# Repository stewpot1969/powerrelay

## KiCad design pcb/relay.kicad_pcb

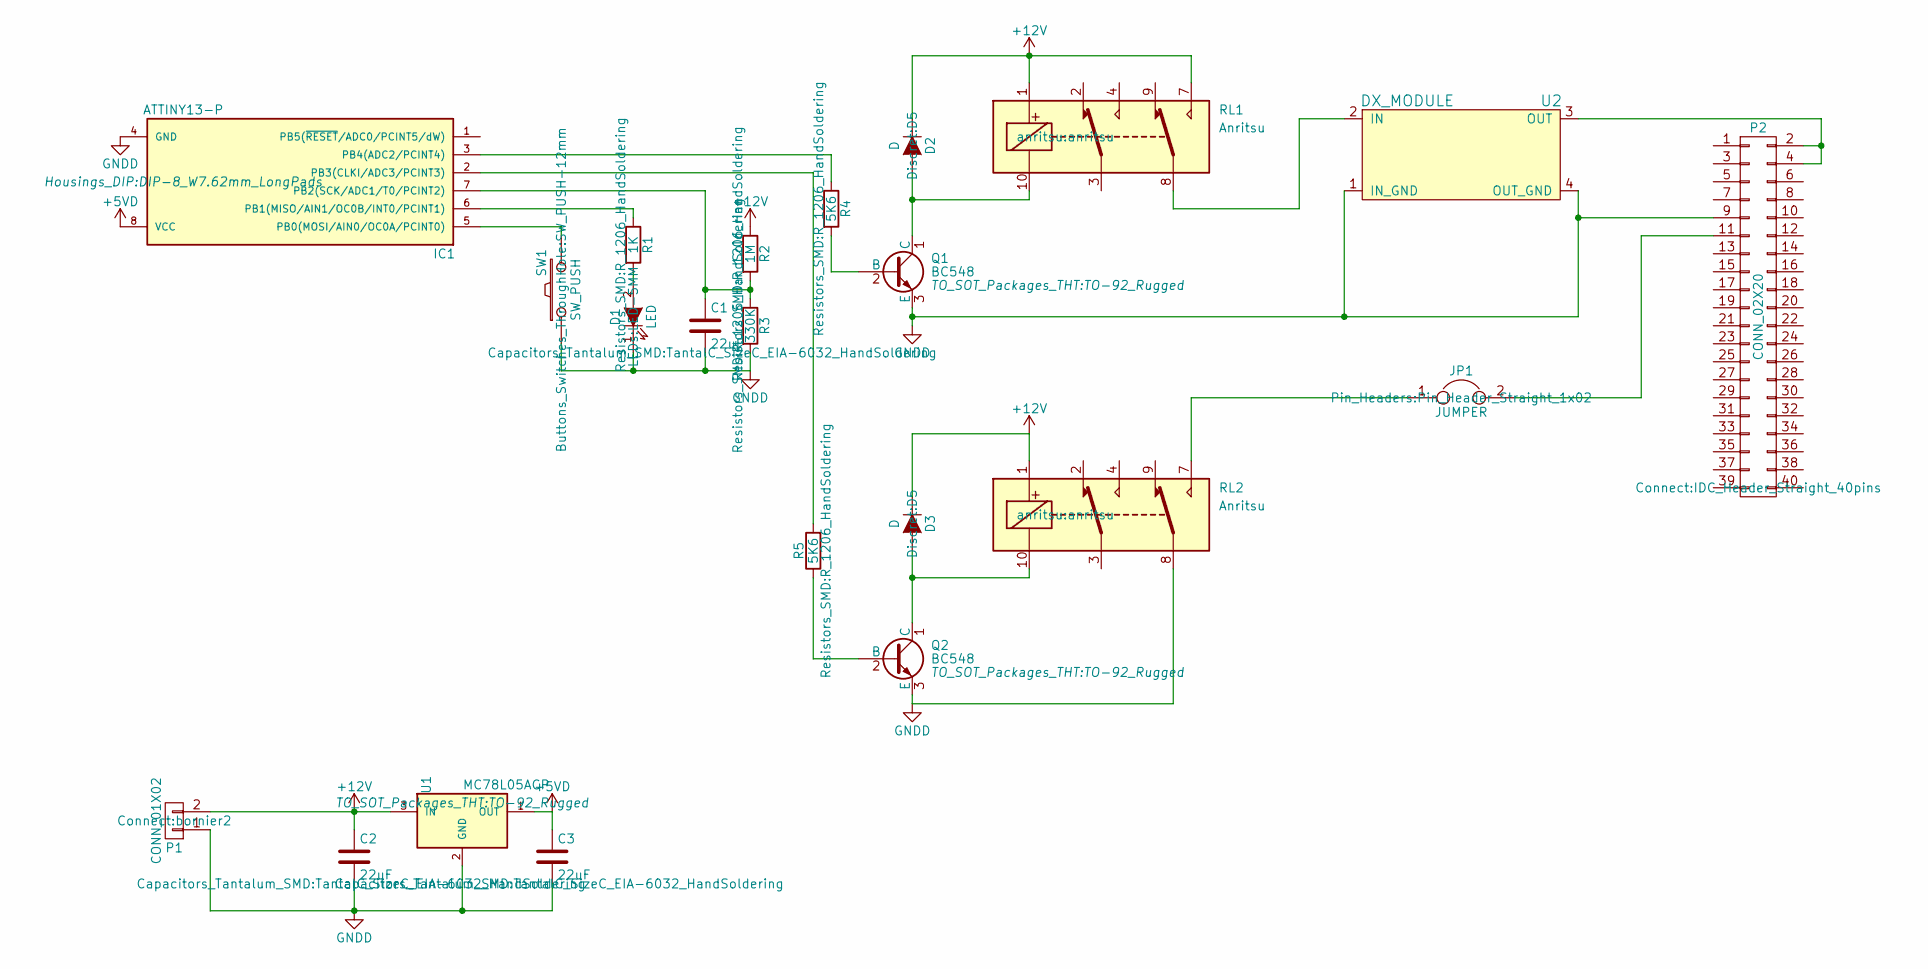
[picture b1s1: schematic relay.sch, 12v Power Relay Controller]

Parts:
C1, C2, C3: 22uF; TantalC_SizeC_EIA-6032_HandSoldering
D1: LED; LED-5MM
D2, D3: D; D5
IC1: ATTINY13-P; DIP-8_W7.62mm_LongPads
JP1: JUMPER; Pin_Header_Straight_1x02
P1: CONN_01X02; bornier2
P2: CONN_02X20; IDC_Header_Straight_40pins
Q1, Q2: BC548; TO-92_Rugged
R1: 1K; R_1206_HandSoldering
R2: 1M; R_1206_HandSoldering
R3: 330K; R_1206_HandSoldering
R4, R5: 5K6; R_1206_HandSoldering
RL1, RL2: Anritsu; anritsu
SW1: SW_PUSH; SW_PUSH-12mm
U1: MC78L05ACP; TO-92_Rugged
U2: DX_MODULE; dx_module

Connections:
+5VD: C3.1, IC1.8 (VCC), U1.1 (OUT)
+12V: C2.1, D2.1 (K), D3.1 (K), P1.2, R2.1, RL1.1, RL1.7, RL2.1, U1.3 (IN)
GNDD: C1.2, C2.2, C3.2, D1.1 (K), IC1.4 (GND), P1.1, P2.9, Q1.3 (E), Q2.3 (E), R3.2, RL2.8, SW1.1, U1.2 (GND), U2.1 (IN_GND), U2.4 (OUT_GND)
unnamed: C1.1, IC1.7 (PB2(SCK/ADC1/T0/PCINT2)), R2.2, R3.1
unnamed: D1.2 (A), R1.2
unnamed: D2.2 (A), Q1.1 (C), RL1.10
unnamed: D3.2 (A), Q2.1 (C), RL2.10
unnamed: IC1.2 (PB3(CLKI/ADC3/PCINT3)), R5.2
unnamed: IC1.3 (PB4(ADC2/PCINT4)), R4.1
unnamed: IC1.5 (PB0(MOSI/AIN0/OC0A/PCINT0)), SW1.2
unnamed: IC1.6 (PB1(MISO/AIN1/OC0B/INT0/PCINT1)), R1.1
unnamed: JP1.1, RL2.7
unnamed: JP1.2, P2.11
unnamed: P2.2, P2.4, U2.3 (OUT)
unnamed: Q1.2 (B), R4.2
unnamed: Q2.2 (B), R5.1
unnamed: RL1.8, U2.2 (IN)

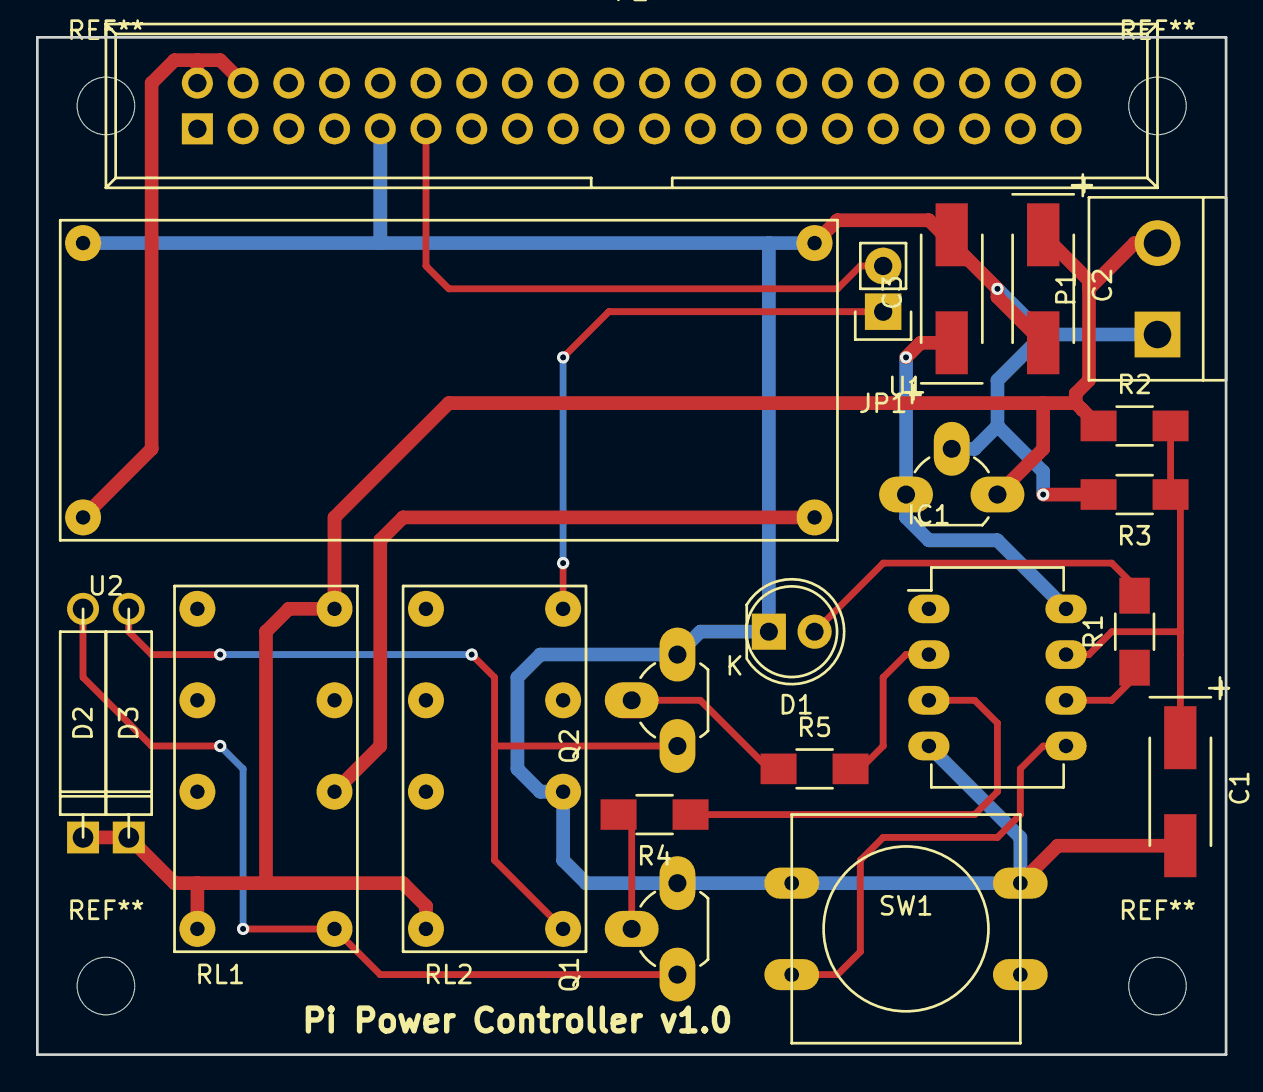
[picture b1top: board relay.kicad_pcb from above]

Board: 2 copper layers, 66.0 x 56.5 mm, 22 parts (0 on the bottom side), 17 nets.

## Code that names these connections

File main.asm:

;  file to control a relay

.nolist
.include "tn13def.inc"
.list

; VOLTAGE LEVELS
; ADC result = 50.8*voltage - 2.39
.define   V_HIGH            668     ; ~13.2V
.define   V_LOW             617     ; ~12.2V

; temp reg for things
.def  scratch = r23
; timer countdown for state changes etc
.def  count   = r24
.define   COUNT_PRE_ON      10   ; seconds of engine-on volts before bootup
.define   COUNT_PRE_OFF     20    ; seconds from shutdown relay on to power off
.define   COUNT_PRE_SHUT    180     ; secs of engine-off volts before shutdown

; prescaler for second counter
.def  count2  = r25
.define   COUNT2_PRESCALE   4

; state of the switch
.def  state   = r26
.define   STATE_IDLE        1   ; resting state
.define   STATE_PRE_ON      2   ; engine started
.define   STATE_ON          4   ; power on to Pi
.define   STATE_PRE_SHUT    8   ; engine turned off, Pi still running
.define   STATE_PRE_OFF     16  ; shutdown relay on, Pi shutting down
.define   STATE_MANUAL      32  ; button has been pressed

; state of the voltage input
.def  v_state = r27
.define   V_STATE_SICK      1     ; <12.2V - battery getting down
.define   V_STATE_OK        2     ; 12.2-13.2V  - engine off, battery OK
.define   V_STATE_HIGH      4     ; >13.2V - engine running
.define   V_STATE_BUTTON    8     ; button pushed


.macro    set_output
    in    r16,DDR@0
    ori   r16,1<<@1
    out   DDR@0,r16
.endm
.macro    set_pullup
    in    r16,PORT@0
    ori   r16,1<<@1
    out   PORT@0,r16
.endm
.macro    set_high
    in    r16,PORT@0
    ori   r16,1<<@1
    out   PORT@0,r16
.endm
.macro    set_low
    in    r16,PORT@0
    andi  r16,255-(1<<@1)
    out   PORT@0,r16
.endm

.dseg
.org  SRAM_START

; myval:    .byte 1

.cseg
.org          0x0000


reset:
    ldi     r16,low(RAMEND)
    out     SPL,r16

    ; setup I/O
    ; 1: _reset
    ; 2: PB3 - relay out
    ; 3: PB4 - 2nd relay?
    ; 4: GND
    ; 5: PB0 - button
    ; 6: PB1 - indicator LED
    ; 7: PB2 - ADC1 - sys V in
    ; 8: 5V
    ldi   r16,(1<<1)|(1<<3)|(1<<4)
    out   DDRB,r16
    ;set_output  B,1       ; PB1 LED out
    ;set_output  B,3       ; PB3 relay 1 out
    ;set_output  B,4       ; PB4 relay 2 out
    set_pullup  B,0       ; PB0 button pullup

    ; setup ADC (Vref=Vcc, /8 prescaler (125kHz))
    ; PB2 (ADC1), ADLAR=0
    
    ldi     r16,1     ; Vref=Vcc, ADLAR=0, MUX1=1 (ADC1 PB2)
    out     ADMUX,r16
    
    ldi     r16,(1<<ADEN)+3 ; enable ADC, /8
    out     ADCSRA,r16
    
    ; setup timer0
    ; compare output modes normal, WGM=CTC
    ldi     r16,0b00000010
    out     TCCR0A,r16
    ; WGM=CTC, clock prescaler = 1024
    ldi     r16,0b00000101
    out     TCCR0B,r16
    ; overflow every 250 cycles = 0.5 seconds
    ldi     r16,250
    out     OCR0A,r16

    ; prepare states and stuff for the loop
    ldi     count,-1        ; timer off
    ldi     state,STATE_IDLE    ; state=IDLE
    ldi     count2,COUNT2_PRESCALE  ; load prescaler

loop:
    
    ; step 1: wait for the interrupt flag to be set
    in    r16,TIFR0
    sbrs  r16,OCF0A
    rjmp  loop
    
    ; step 2: clear interrupt flag
    ldi   r16,1<<OCF0A
    out   TIFR0,r16

    ; step 3 - read ADC
    ldi     r16,(1<<ADEN)+(1<<ADSC)+1   ; start conversion
    out     ADCSRA,r16
wfadc:
    in      r16,ADCSRA
    andi    r16,(1<<ADIF)     ; check if ADIF is set (ADC complete)
    breq    wfadc

    ; step 4 - look at the voltage
    in      r16,ADCL
    in      r17,ADCH
    ldi     r18,low(V_HIGH)
    ldi     r19,high(V_HIGH)
    cp      r16,r18     ; subtract V_HIGH from ADC
    cpc     r17,r19
    brcs    s4_1    ; branch if ADC < V_HIGH
    ldi     v_state,V_STATE_HIGH
    rjmp    s5
s4_1:
    ldi     r18,low(V_LOW)
    ldi     r19,high(V_LOW)
    cp      r16,r18   ; subtract V_LOW from ADC
    cpc     r17,r19
    brcs    s4_2      ; branch if ADC < V_LOW
    ldi     v_state,V_STATE_OK
    rjmp    s5
s4_2:
    ldi     v_state,V_STATE_SICK
    
    ; step 5  - check button, decrement timer prescaler and timer
s5:
    in    r16,PINB
    andi  r16,1     ; check bit 0
    brne  s5_1      ; PINB.0=1 = no button
    ori   v_state,V_STATE_BUTTON
s5_1:
    dec   count2
    brne  loop      ; no prescale zero? All done for this time
    ldi   count2,COUNT2_PRESCALE    ; reload prescaler
    cpi   count,-1      ; count=-1 means counter not being used
    breq  s6
    dec   count


    ; step 6 - split out based on state
s6:
    ldi   ZL,low(calltable*2)
    ldi   ZH,high(calltable*2)
s6_1:
    lpm   r16,Z+    ; r16=V_STATE mask
    tst   r16
    breq  loop      ; table ends in zero
    lpm   r17,Z+    ; r17=STATE mask
    lpm   YL,Z+     ; save subroutine address in Y
    lpm   YH,Z+
    and   r16,v_state   ; and v_state with v_state mask
    breq  s6_1      ; no overlap? go to next entry in calltable
    and   r17,state     ; now check state mask
    breq  s6_1        ; no overlap? next entry
    mov   ZH,YH       ; move Y to Z
    mov   ZL,YL
    icall           ; call subroutine pointed to by Z
    rjmp  loop    

;========================================================
; SUBROUTINES POINTED TO BY CALLTABLE:

idleoff:    ; go into idle mode
  ldi   state,STATE_IDLE
  ldi   count,-1
  in    r16,PORTB
  andi  r16,0b11100101  ; 1,3,4 off = power,shutdown,LED
  out   PORTB,r16
  ret  
  
preshut:    ; sets state=PRE_SHUT
  ldi   state,STATE_PRE_SHUT
  ldi   count,COUNT_PRE_SHUT
  ret
  
preoff:   ;state=PRE_SHUT,Vok
  tst   count     ; timer before setting shutdown relay
  brne  preoff_2
  ldi   state,STATE_PRE_OFF
  ldi   count,COUNT_PRE_OFF
  set_high  B,3   ; shutdown relay on
preoff_2:
  ret

timer_idle:     ; state=PRE_OFF,Vok
  tst   count     ; wait for timer to run out before going idle
  brne  timer_idle_2
  rcall idleoff
timer_idle_2:
  ret

preon:      ; state=IDLE, Vhigh
  ldi   state,STATE_PRE_ON
  ldi   count,COUNT_PRE_ON
  ret
  
pi_on:    ; turn the Pi on
  tst   count   ; do nothing until timer runs out
  brne  pi_on_2
  ldi   state,STATE_ON
  ldi   count,-1
  set_high  B,1   ; LED on
  set_high  B,4   ; Pi power on
pi_on_2:
  ret

cancel_shut:    ; goes from state preshut to state on i.e. engine restarts
  ldi   state,STATE_ON
  ldi   count,-1
  ret

manual_on:
  set_high  B,1   ; LED ON
  set_high  B,4   ; Pi power on
  ldi   state,STATE_MANUAL
  ldi   count,5
  ret

manual_off:
  cpi   count,-1
  brne  eomanualoff
  ldi   count,0
  rcall preoff
eomanualoff:
  ret

calltable:
  .db   V_STATE_BUTTON,STATE_IDLE
    .dw manual_on
  .db   V_STATE_BUTTON,STATE_MANUAL
    .dw manual_off
  .db   V_STATE_SICK,STATE_PRE_ON|STATE_ON|STATE_PRE_SHUT|STATE_PRE_OFF
    .dw idleoff
  .db   V_STATE_OK,STATE_PRE_ON
    .dw idleoff
  .db   V_STATE_OK,STATE_ON
    .dw preshut
  .db   V_STATE_OK,STATE_PRE_SHUT
    .dw preoff    
  .db   V_STATE_OK,STATE_PRE_OFF
    .dw timer_idle    
  .db   V_STATE_HIGH,STATE_IDLE
    .dw preon
  .db   V_STATE_HIGH,STATE_PRE_ON
    .dw pi_on
  .db   V_STATE_HIGH,STATE_PRE_SHUT
    .dw cancel_shut
  .db   0,0
;################################################################

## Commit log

2016-08-17 Random playing for learning purposes
2016-08-17 Removed tempfile.txt
2016-08-17 Minor changes to bit definitions
2016-08-17 Added prog.sh, upped the flash rate a bit.
2016-09-06 Added PCB files.
2016-09-08 More work on PCB
2016-09-08 Added RPi dimensions.
2016-09-08 Changed footprints on PCB.
2016-09-09 Final version of PCB sent to OSHPark.
2016-10-07 Debug version
2016-10-09 LED debug - Vlow=off, Vok=flash, Vhigh=on
2016-10-09 Debug version - LED flashes every second, shortened wait periods.
2016-10-10 Test of refactored code.
2016-10-22 Final working version 20161022
